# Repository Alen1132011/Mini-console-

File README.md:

# Mini Console v1

Mini Console v1 is a small DIY retro gaming console built completely from scratch. The idea was to make a fun little device to kill some boredom, designed in KiCad and programmed for the ESP32-C3.

## Features
- **Two Games**: Currently features built-in classic versions of *Flappy Bird* and *Snake*.
- **Menu & Settings**: Simple menu system to select games and toggle sound on or off.
- **Portable Power**: Uses a TP4056 lithium battery charger and MT3608 boost module so the console runs on battery.
- **Mechanical Controls**: Six push buttons for movement, jumps, and selections.

## Hardware & Bill of Materials (BOM)

| Component | Quantity | Description |
| :--- | :--- | :--- |
| ESP32-C3 SuperMini | 1 | Microcontroller |
| 0.96" I2C OLED Display | 1 | Screen for graphics rendering |
| THT Push Buttons (6mm) | 6 | Mechanical controls |
| TP4056 Battery Charger Module | 1 | Lithium battery charging |
| MT3608 Boost Module | 1 | 5V voltage step-up |
| Buzzer | 1 | Sound output |
| Ceramic Capacitors (100nF) | 2 | Decoupling / Filtering |
| Electrolytic Capacitor (10µF) | 1 | Power filtering |
| Slide Switch (SPST) | 1 | Power toggle switch |
| JST XH Connectors | Multiple | Cable connections |
| Custom Double-Sided PCB | 1 | Circuit board designed in KiCad |

## Software & Code
- Written in the Arduino IDE environment using the `Adafruit_GFX` and `Adafruit_SSD1306` libraries for screen rendering.
- Uses straightforward logic for switching between menus, games, and sound settings.

## Note: 
The project is not fully completed yet. There are only two games right now, but as soon as the physical product arrives and I run tests, I plan to add more games and further polish the project setup.

>

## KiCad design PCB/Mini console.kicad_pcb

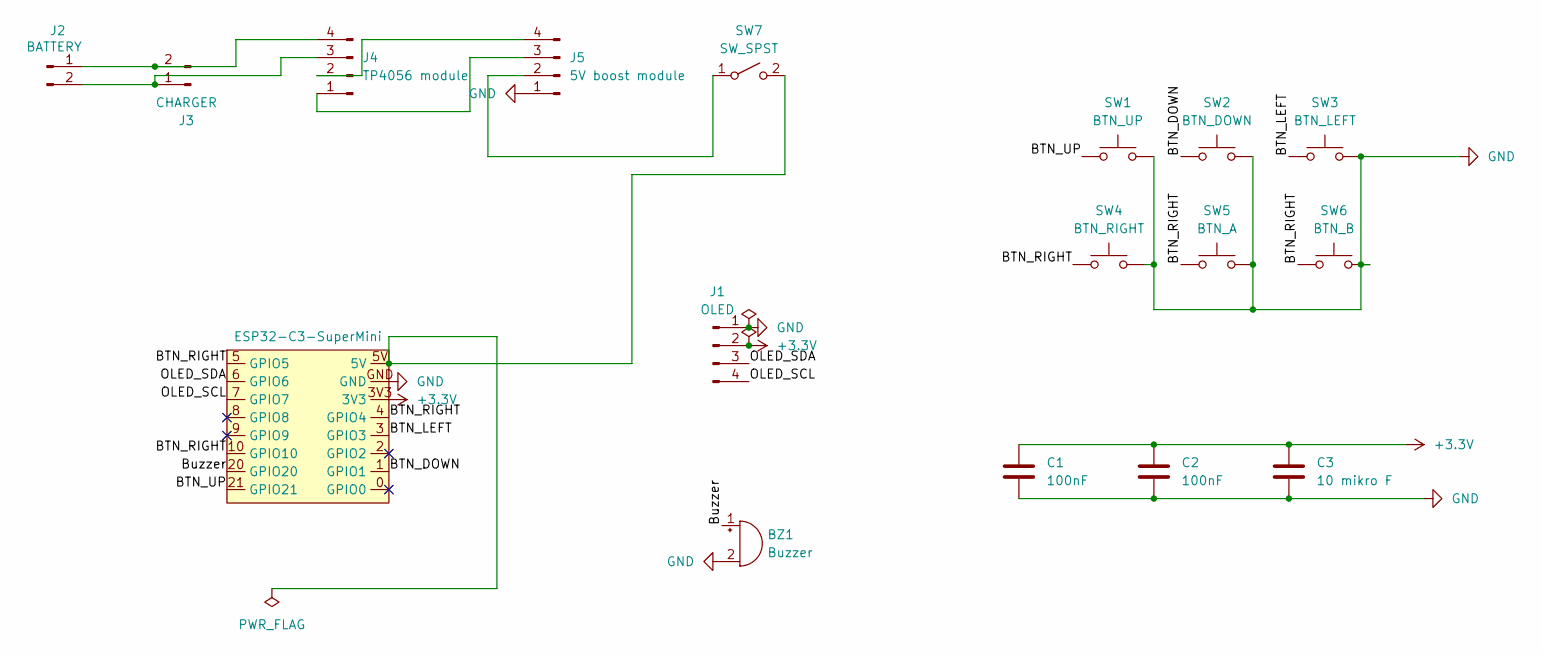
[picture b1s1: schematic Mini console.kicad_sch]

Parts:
BZ1: Buzzer; Buzzer_12x9.5RM7.6
C1, C2: 100nF; C_Disc_D5.0mm_W2.5mm_P5.00mm
C3: 10 mikro F; CP_Radial_D5.0mm_P2.00mm
J1: OLED; ER_OLEDM0.91_1x-I2C
J2: BATTERY; JST_XH_B2B-XH-A_1x02_P2.50mm_Vertical
J3: CHARGER; JST_XH_B2B-XH-A_1x02_P2.50mm_Vertical
J4: TP4056 module; 4056E_LiIon_loader
J5: 5V boost module; MT3608_module
SW1: BTN_UP; SW_PUSH_6mm_H5mm
SW2: BTN_DOWN; SW_PUSH_6mm_H5mm
SW3: BTN_LEFT; SW_PUSH_6mm_H5mm
SW4: BTN_RIGHT; SW_PUSH_6mm_H5mm
SW5: BTN_A; SW_PUSH_6mm_H5mm
SW6: BTN_B; SW_PUSH_6mm_H5mm
SW7: SW_SPST; SW_DIP_SPSTx01_Slide_6.7x4.1mm_W6.73mm_P2.54mm_LowProfile_J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
U2: ESP32-C3-SuperMini

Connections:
+3.3V: C1.1, C2.1, C3.1, J1.2, U2.3V3
/BTN_DOWN: SW2.1, U2.1 (GPIO1)
/BTN_LEFT: SW3.1, U2.3 (GPIO3)
/BTN_RIGHT: SW4.1, SW5.1, SW6.1, U2.4 (GPIO4), U2.5 (GPIO5), U2.10 (GPIO10)
/BTN_UP: SW1.1, U2.21 (GPIO21)
/Buzzer: BZ1.1 (+), U2.20 (GPIO20)
/OLED_SCL: J1.4, U2.7 (GPIO7)
/OLED_SDA: J1.3, U2.6 (GPIO6)
GND: BZ1.2 (-), C1.2, C2.2, C3.2, J1.1, J5.1, SW1.2, SW2.2, SW3.2, SW4.2, SW5.2, SW6.2, U2.GND
unnamed: J2.1, J3.2, J4.4
unnamed: J2.2, J3.1, J4.3
unnamed: J4.1, J5.3
unnamed: J4.2, J5.4
unnamed: J5.2, SW7.1 (A)
unnamed: SW7.2 (B), U2.5V

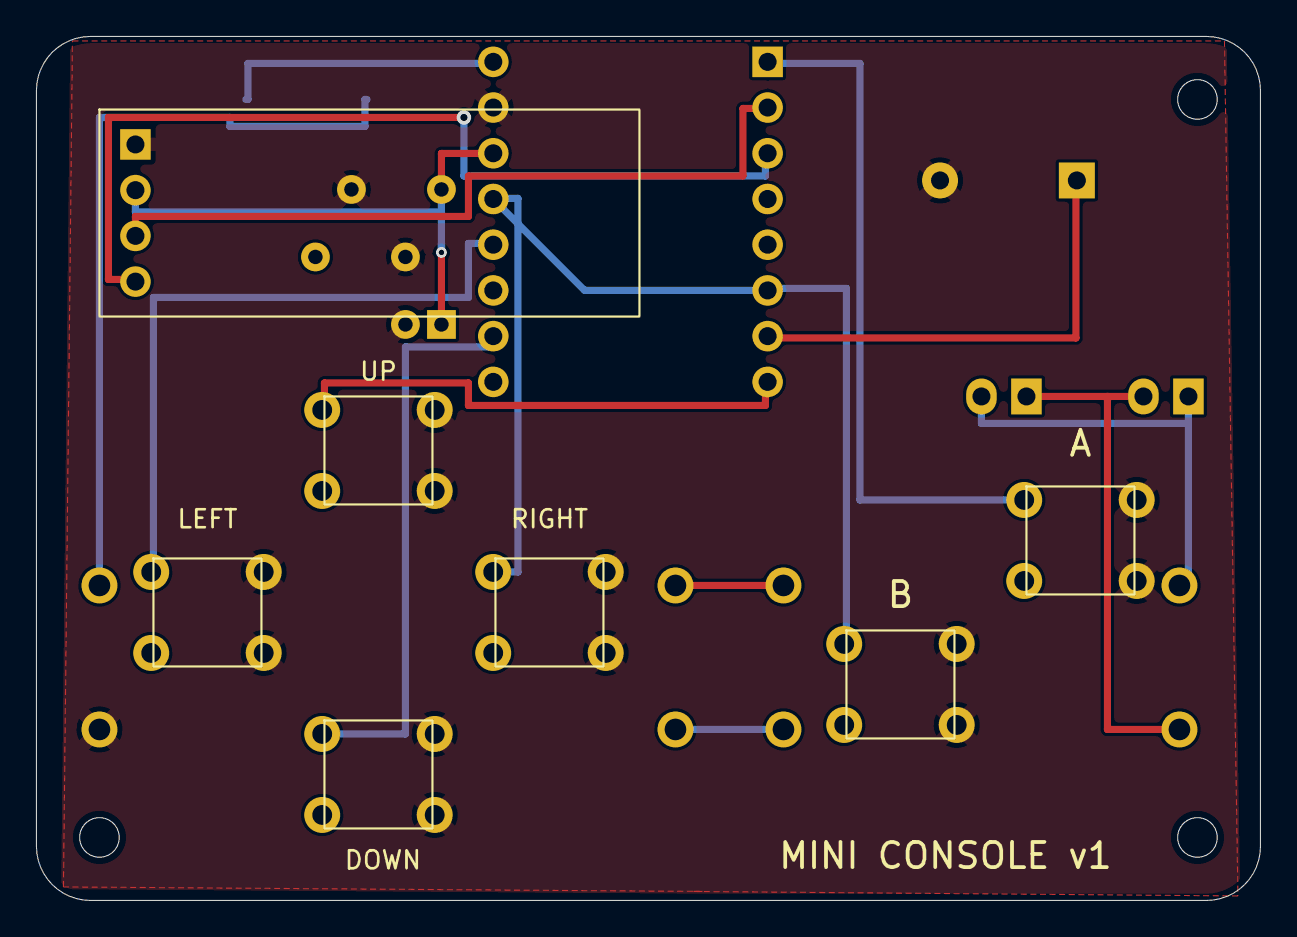
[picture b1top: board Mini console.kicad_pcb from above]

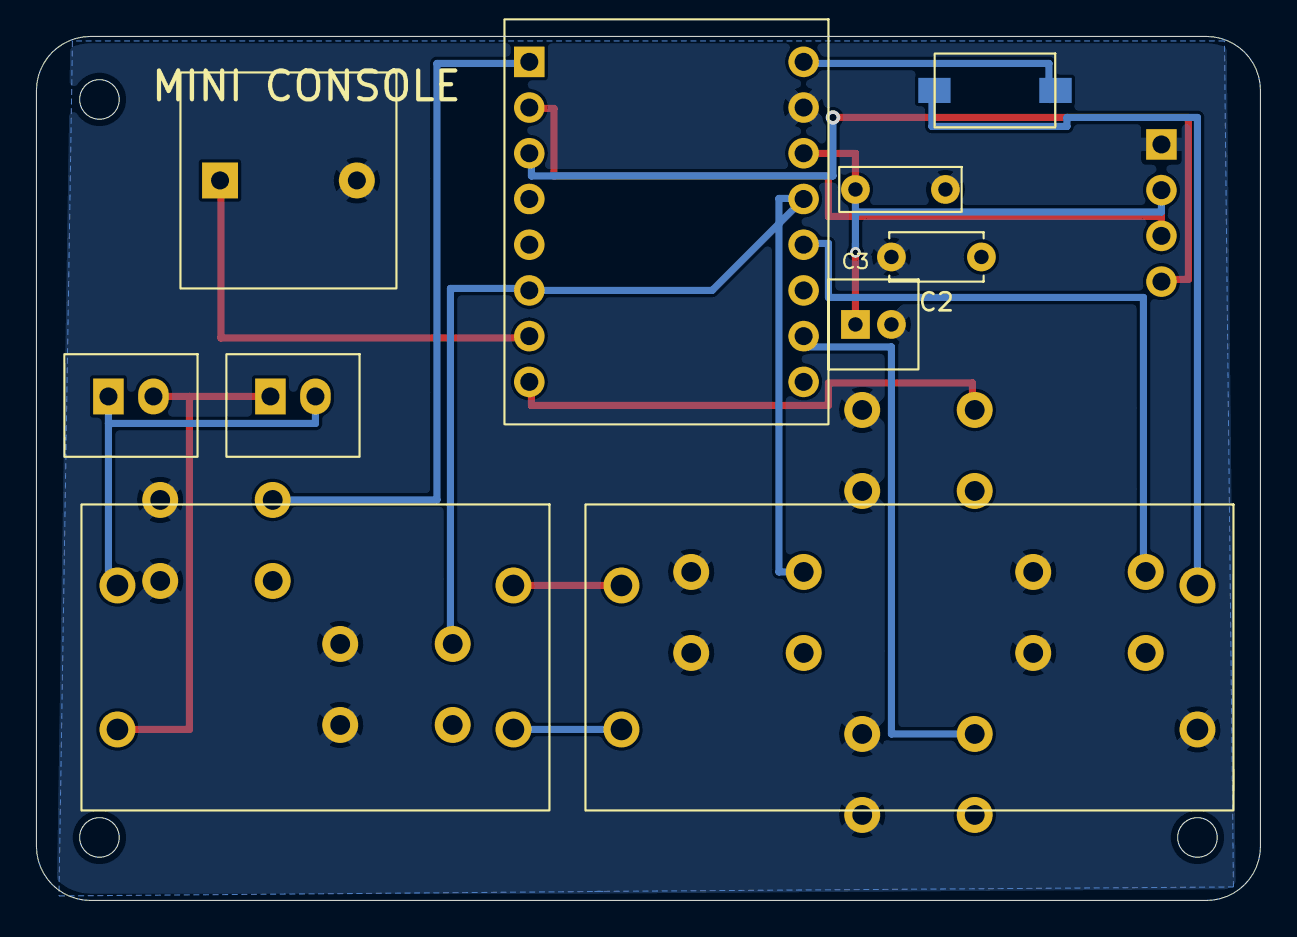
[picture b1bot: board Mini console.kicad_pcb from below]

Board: 2 copper layers, 68.0 x 48.0 mm, 17 parts (10 on the bottom side), 15 nets.
